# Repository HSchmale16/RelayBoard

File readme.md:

# Relay Board

**THESE DESIGNS ARE NO WHERE NEAR DONE.**

These are designs for a 32 Channel Relay Board that can be driven with
small microcontrollers, such as the Arduino and the BeagleBone.
The included designs are for KiCad.

These designs are provided with **NO WARRANTY WHATSOEVER**. No liability
is assumed by the designer of these circuits.

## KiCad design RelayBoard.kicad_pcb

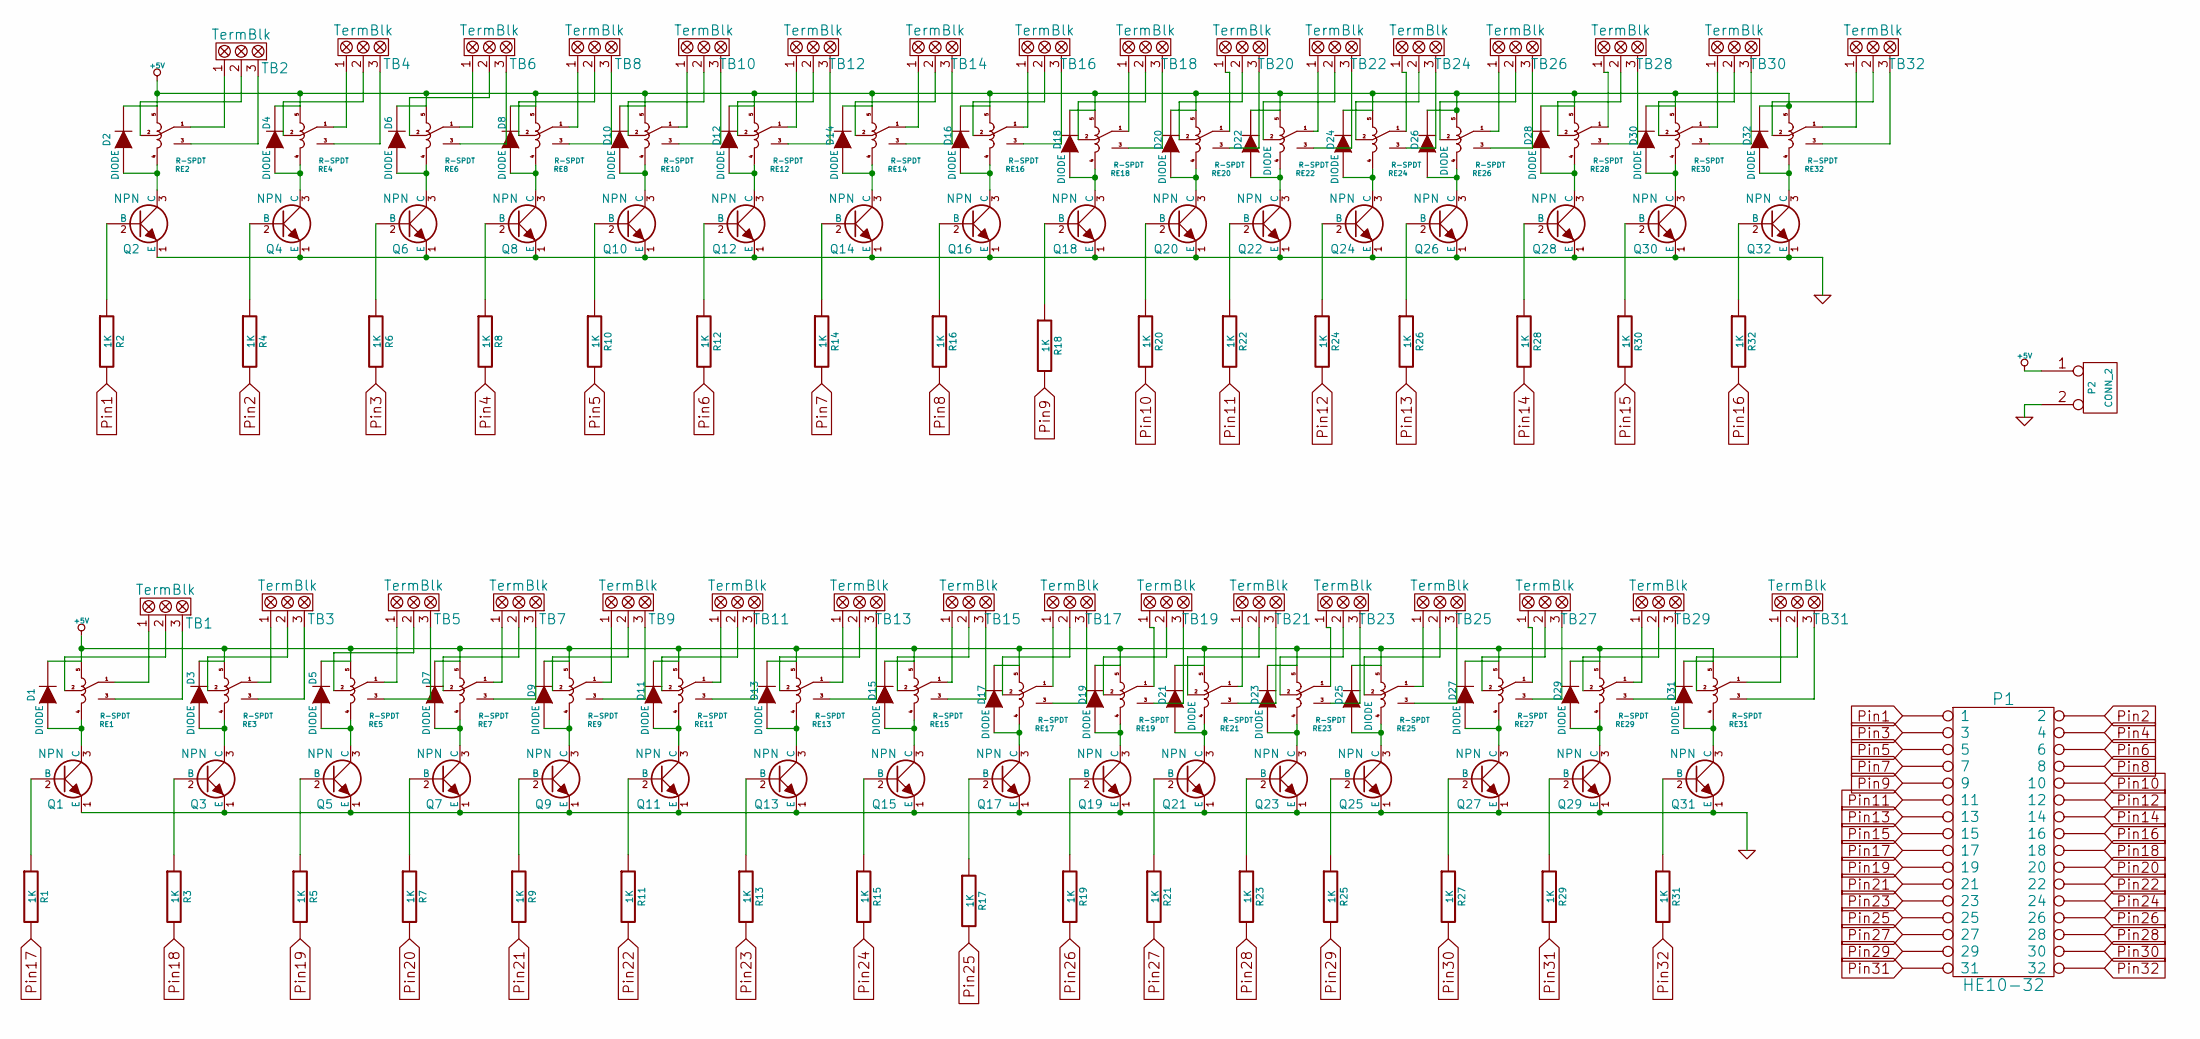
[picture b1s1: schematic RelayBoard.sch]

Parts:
D1, D2, D3, D4, D5, D6, D7, D8, D9, D10, D11, D12, D13, D14, D15, D16, D17, D18, D19, D20, D21, D22, D23, D24, D25, D26, D27, D28, D29, D30, D31, D32: DIODE
P1: HE10-32
P2: CONN_2
Q1, Q2, Q3, Q4, Q5, Q6, Q7, Q8, Q9, Q10, Q11, Q12, Q13, Q14, Q15, Q16, Q17, Q18, Q19, Q20, Q21, Q22, Q23, Q24, Q25, Q26, Q27, Q28, Q29, Q30, Q31, Q32: NPN
R1, R2, R3, R4, R5, R6, R7, R8, R9, R10, R11, R12, R13, R14, R15, R16, R17, R18, R19, R20, R21, R22, R23, R24, R25, R26, R27, R28, R29, R30, R31, R32: 1K
RE1, RE2, RE3, RE4, RE5, RE6, RE7, RE8, RE9, RE10, RE11, RE12, RE13, RE14, RE15, RE16, RE17, RE18, RE19, RE20, RE21, RE22, RE23, RE24, RE25, RE26, RE27, RE28, RE29, RE30, RE31, RE32: R-SPDT
TB1, TB2, TB3, TB4, TB5, TB6, TB7, TB8, TB9, TB10, TB11, TB12, TB13, TB14, TB15, TB16, TB17, TB18, TB19, TB20, TB21, TB22, TB23, TB24, TB25, TB26, TB27, TB28, TB29, TB30, TB31, TB32: TermBlk

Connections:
+5V: D1.2 (K), D2.2 (K), D3.2 (K), D4.2 (K), D5.2 (K), D6.2 (K), D7.2 (K), D8.2 (K), D9.2 (K), D10.2 (K), D11.2 (K), D12.2 (K), D13.2 (K), D14.2 (K), D15.2 (K), D16.2 (K), D17.2 (K), D18.2 (K), D19.2 (K), D20.2 (K), D21.2 (K), D22.2 (K), D23.2 (K), D24.2 (K), D25.2 (K), D26.2 (K), D27.2 (K), D28.2 (K), D29.2 (K), D30.2 (K), D31.2 (K), D32.2 (K), P2.1, RE1.5, RE2.5, RE3.5, RE4.5, RE5.5, RE6.5, RE7.5, RE8.5, RE9.5, RE10.5, RE11.5, RE12.5, RE13.5, RE14.5, RE15.5, RE16.5, RE17.5, RE18.5, RE19.5, RE20.5, RE21.5, RE22.5, RE23.5, RE24.5, RE25.5, RE26.5, RE27.5, RE28.5, RE29.5, RE30.5, RE31.5, RE32.5
GND: P2.2 (PM), Q1.1 (E), Q2.1 (E), Q3.1 (E), Q4.1 (E), Q5.1 (E), Q6.1 (E), Q7.1 (E), Q8.1 (E), Q9.1 (E), Q10.1 (E), Q11.1 (E), Q12.1 (E), Q13.1 (E), Q14.1 (E), Q15.1 (E), Q16.1 (E), Q17.1 (E), Q18.1 (E), Q19.1 (E), Q20.1 (E), Q21.1 (E), Q22.1 (E), Q23.1 (E), Q24.1 (E), Q25.1 (E), Q26.1 (E), Q27.1 (E), Q28.1 (E), Q29.1 (E), Q30.1 (E), Q31.1 (E), Q32.1 (E)
unnamed: D1.1 (A), Q1.3 (C), RE1.4
unnamed: D2.1 (A), Q2.3 (C), RE2.4
unnamed: D3.1 (A), Q3.3 (C), RE3.4
unnamed: D4.1 (A), Q4.3 (C), RE4.4
unnamed: D5.1 (A), Q5.3 (C), RE5.4
unnamed: D6.1 (A), Q6.3 (C), RE6.4
unnamed: D7.1 (A), Q7.3 (C), RE7.4
unnamed: D8.1 (A), Q8.3 (C), RE8.4
unnamed: D9.1 (A), Q9.3 (C), RE9.4
unnamed: D10.1 (A), Q10.3 (C), RE10.4
unnamed: D11.1 (A), Q11.3 (C), RE11.4
unnamed: D12.1 (A), Q12.3 (C), RE12.4
unnamed: D13.1 (A), Q13.3 (C), RE13.4
unnamed: D14.1 (A), Q14.3 (C), RE14.4
unnamed: D15.1 (A), Q15.3 (C), RE15.4
unnamed: D16.1 (A), Q16.3 (C), RE16.4
unnamed: D17.1 (A), Q17.3 (C), RE17.4
unnamed: D18.1 (A), Q18.3 (C), RE18.4
unnamed: D19.1 (A), Q19.3 (C), RE19.4
unnamed: D20.1 (A), Q20.3 (C), RE20.4
unnamed: D21.1 (A), Q21.3 (C), RE21.4
unnamed: D22.1 (A), Q22.3 (C), RE22.4
unnamed: D23.1 (A), Q23.3 (C), RE23.4
unnamed: D24.1 (A), Q24.3 (C), RE24.4
unnamed: D25.1 (A), Q25.3 (C), RE25.4
unnamed: D26.1 (A), Q26.3 (C), RE26.4
unnamed: D27.1 (A), Q27.3 (C), RE27.4
unnamed: D28.1 (A), Q28.3 (C), RE28.4
unnamed: D29.1 (A), Q29.3 (C), RE29.4
unnamed: D30.1 (A), Q30.3 (C), RE30.4
unnamed: D31.1 (A), Q31.3 (C), RE31.4
unnamed: D32.1 (A), Q32.3 (C), RE32.4
unnamed: Q1.2 (B), R1.1
unnamed: Q2.2 (B), R2.1
unnamed: Q3.2 (B), R3.1
unnamed: Q4.2 (B), R4.1
unnamed: Q5.2 (B), R5.1
unnamed: Q6.2 (B), R6.1
unnamed: Q7.2 (B), R7.1
unnamed: Q8.2 (B), R8.1
unnamed: Q9.2 (B), R9.1
unnamed: Q10.2 (B), R10.1
unnamed: Q11.2 (B), R11.1
unnamed: Q12.2 (B), R12.1
unnamed: Q13.2 (B), R13.1
unnamed: Q14.2 (B), R14.1
unnamed: Q15.2 (B), R15.1
unnamed: Q16.2 (B), R16.1
unnamed: Q17.2 (B), R17.1
unnamed: Q18.2 (B), R18.1
unnamed: Q19.2 (B), R19.1
unnamed: Q20.2 (B), R20.1
unnamed: Q21.2 (B), R21.1
unnamed: Q22.2 (B), R22.1
unnamed: Q23.2 (B), R23.1
unnamed: Q24.2 (B), R24.1
unnamed: Q25.2 (B), R25.1
unnamed: Q26.2 (B), R26.1
unnamed: Q27.2 (B), R27.1
unnamed: Q28.2 (B), R28.1
unnamed: Q29.2 (B), R29.1
unnamed: Q30.2 (B), R30.1
unnamed: Q31.2 (B), R31.1
unnamed: Q32.2 (B), R32.1
unnamed: RE1.1, TB1.1
unnamed: RE1.2, TB1.2
unnamed: RE1.3, TB1.3
unnamed: RE2.1, TB2.1
unnamed: RE2.2, TB2.2
unnamed: RE2.3, TB2.3
unnamed: RE3.1, TB3.1
unnamed: RE3.2, TB3.2
unnamed: RE3.3, TB3.3
unnamed: RE4.1, TB4.1
unnamed: RE4.2, TB4.2
unnamed: RE4.3, TB4.3
unnamed: RE5.1, TB5.1
unnamed: RE5.2, TB5.2
unnamed: RE5.3, TB5.3
unnamed: RE6.1, TB6.1
unnamed: RE6.2, TB6.2
unnamed: RE6.3, TB6.3
unnamed: RE7.1, TB7.1
unnamed: RE7.2, TB7.2
unnamed: RE7.3, TB7.3
unnamed: RE8.1, TB8.1
unnamed: RE8.2, TB8.2
unnamed: RE8.3, TB8.3
unnamed: RE9.1, TB9.1
unnamed: RE9.2, TB9.2
unnamed: RE9.3, TB9.3
unnamed: RE10.1, TB10.1
unnamed: RE10.2, TB10.2
unnamed: RE10.3, TB10.3
unnamed: RE11.1, TB11.1
unnamed: RE11.2, TB11.2
unnamed: RE11.3, TB11.3
unnamed: RE12.1, TB12.1
unnamed: RE12.2, TB12.2
unnamed: RE12.3, TB12.3
unnamed: RE13.1, TB13.1
unnamed: RE13.2, TB13.2
unnamed: RE13.3, TB13.3
unnamed: RE14.1, TB14.1
unnamed: RE14.2, TB14.2
unnamed: RE14.3, TB14.3
unnamed: RE15.1, TB15.1
unnamed: RE15.2, TB15.2
unnamed: RE15.3, TB15.3
unnamed: RE16.1, TB16.1
unnamed: RE16.2, TB16.2
unnamed: RE16.3, TB16.3
unnamed: RE17.1, TB17.1
unnamed: RE17.2, TB17.2
unnamed: RE17.3, TB17.3
unnamed: RE18.1, TB18.1
unnamed: RE18.2, TB18.2
unnamed: RE18.3, TB18.3
unnamed: RE19.1, TB19.1
unnamed: RE19.2, TB19.2
unnamed: RE19.3, TB19.3
unnamed: RE20.1, TB20.1
unnamed: RE20.2, TB20.2
unnamed: RE20.3, TB20.3
unnamed: RE21.1, TB21.1
unnamed: RE21.2, TB21.2
unnamed: RE21.3, TB21.3
unnamed: RE22.1, TB22.1
unnamed: RE22.2, TB22.2
unnamed: RE22.3, TB22.3
unnamed: RE23.1, TB23.1
unnamed: RE23.2, TB23.2
unnamed: RE23.3, TB23.3
unnamed: RE24.1, TB24.1
unnamed: RE24.2, TB24.2
unnamed: RE24.3, TB24.3
unnamed: RE25.1, TB25.1
unnamed: RE25.2, TB25.2
unnamed: RE25.3, TB25.3
unnamed: RE26.1, TB26.1
unnamed: RE26.2, TB26.2
unnamed: RE26.3, TB26.3
unnamed: RE27.1, TB27.1
unnamed: RE27.2, TB27.2
unnamed: RE27.3, TB27.3
unnamed: RE28.1, TB28.1
unnamed: RE28.2, TB28.2
unnamed: RE28.3, TB28.3
unnamed: RE29.1, TB29.1
unnamed: RE29.2, TB29.2
unnamed: RE29.3, TB29.3
unnamed: RE30.1, TB30.1
unnamed: RE30.2, TB30.2
unnamed: RE30.3, TB30.3
unnamed: RE31.1, TB31.1
unnamed: RE31.2, TB31.2
unnamed: RE31.3, TB31.3
unnamed: RE32.1, TB32.1
unnamed: RE32.2, TB32.2
unnamed: RE32.3, TB32.3
Pin1: P1.1, R2.2
Pin2: P1.2, R4.2
Pin3: P1.3, R6.2
Pin4: P1.4, R8.2
Pin5: P1.5, R10.2
Pin6: P1.6, R12.2
Pin7: P1.7, R14.2
Pin8: P1.8, R16.2
Pin9: P1.9, R18.2
Pin10: P1.10, R20.2
Pin11: P1.11, R22.2
Pin12: P1.12, R24.2
Pin13: P1.13, R26.2
Pin14: P1.14, R28.2
Pin15: P1.15, R30.2
Pin16: P1.16, R32.2
Pin17: P1.17, R1.2
Pin18: P1.18, R3.2
Pin19: P1.19, R5.2
Pin20: P1.20, R7.2
Pin21: P1.21, R9.2
Pin22: P1.22, R11.2
Pin23: P1.23, R13.2
Pin24: P1.24, R15.2
Pin25: P1.25, R17.2
Pin26: P1.26, R19.2
Pin27: P1.27, R21.2
Pin28: P1.28, R23.2
Pin29: P1.29, R25.2
Pin30: P1.30, R27.2
Pin31: P1.31, R29.2
Pin32: P1.32, R31.2

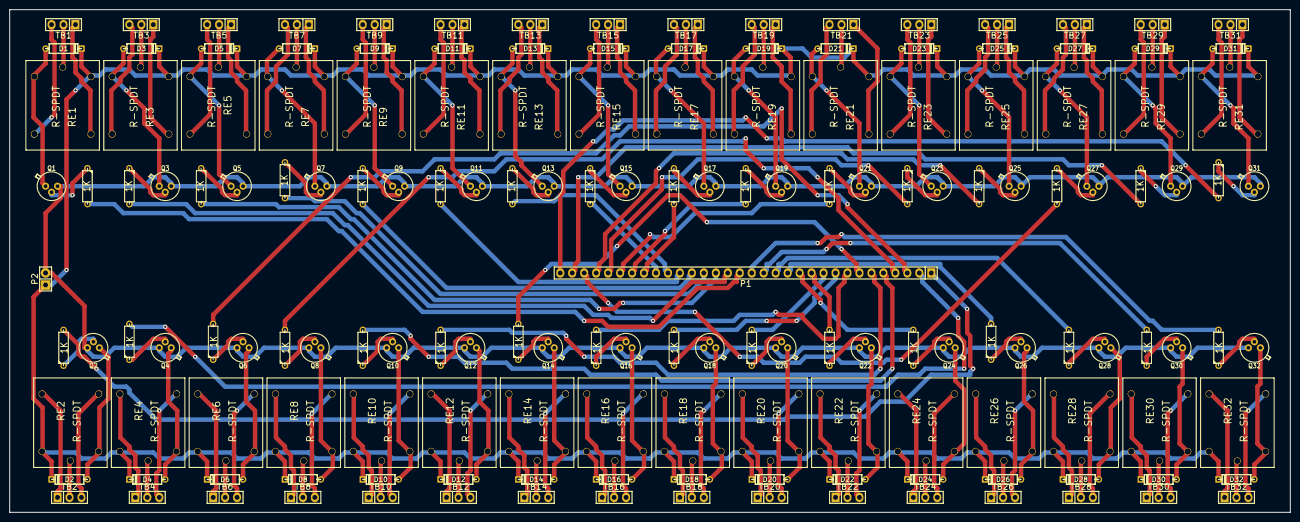
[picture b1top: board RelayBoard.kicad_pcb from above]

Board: 2 copper layers, 271.8 x 106.7 mm, 162 parts (0 on the bottom side), 194 nets.

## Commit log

2015-02-16 Inital Commit
2015-02-16 Added A New Componet to Relay Lib
    * A dioded relay
2015-02-16 Added a parts list
2015-02-16 Parts List
2015-02-16 A New Symbol & More Parts on The List
2015-02-16 New Componets
    * Added Transisters to Diagram
    * Wired Diagram
2015-02-16 Connected to GND
2015-02-16 Terminal Blocks
2015-02-16 More To The Schematic Than Meets The Eye.
2015-02-16 End of worktime
2015-02-17 Finished Pins 1 to 16 connections
2015-02-17 Finished Pins 17 to 24, they are now connected to the bus
2015-02-17 Connected Pins 24 to 32, Still need to resolve electric rules errors
2015-02-17 Finished Schematic
    * Updated Relay Lib Componet Descriptions
    * Generated A NetList
2015-02-17 Part Assocation
    * updated Parts List
    * Updated Parts associations
2015-02-17 Added A PCB File
2015-02-17 Created A Custom Footprint for the relays
    * Finished Part Selection in CVPCB
    * Custom FootPrint Lib
2015-02-17 Started laying out PCB
2015-02-17 Added a readme file
2015-02-17 Added to readme
2015-02-17 Update
    * Updated Readme with a warning.
    * The schematic is nowhere near done as I forgot to include diodes to
    protect against the feedback from relays turning on and off.
2015-02-17 Finished Schematic
    * The schematic now has diodes where needed
    * Parts are associated as needed
2015-02-18 Placed Most of the relays on the PCB
2015-02-18 Placed all of the relays on the PCB.
2015-02-18 Placed all of the terminal blocks on the PCB.
2015-02-18 Did a bunch to the PCB Layout
    * Diode Placement
    * Tracks
    * Commenting
2015-02-18 Added to the parts list
2015-02-18 Changed The Pin headers
    * Changed Pin Headers
    * Placed Most of the resistors on the board
2015-02-18 Finished Placing all parts on PCB
    It's time to route the board
2015-02-18 Changed the footprint of primary input header from 2x16 to 1x32 Due to routing concerns
2015-02-18 Just finished routing
    Autoroute is amazing!
2015-02-18 Stuff
    * Dimension Drawing
    * PCB Edges are now included
